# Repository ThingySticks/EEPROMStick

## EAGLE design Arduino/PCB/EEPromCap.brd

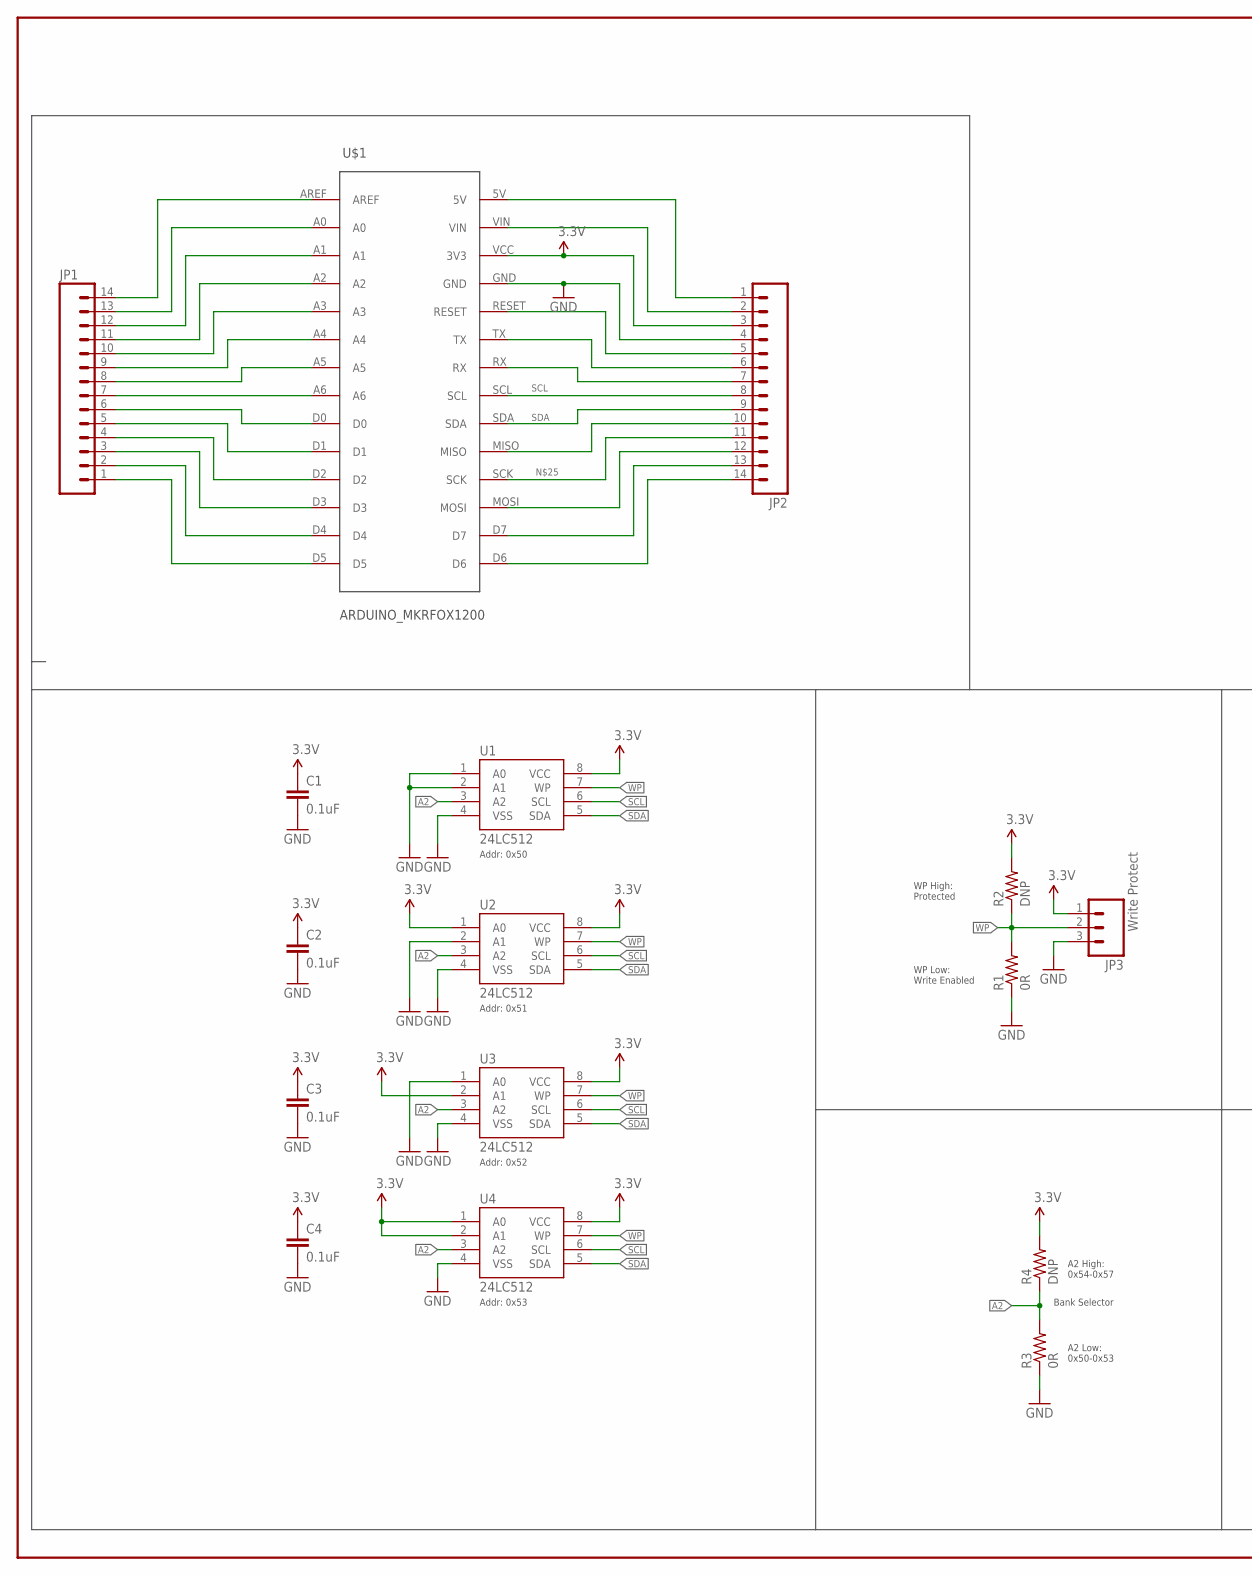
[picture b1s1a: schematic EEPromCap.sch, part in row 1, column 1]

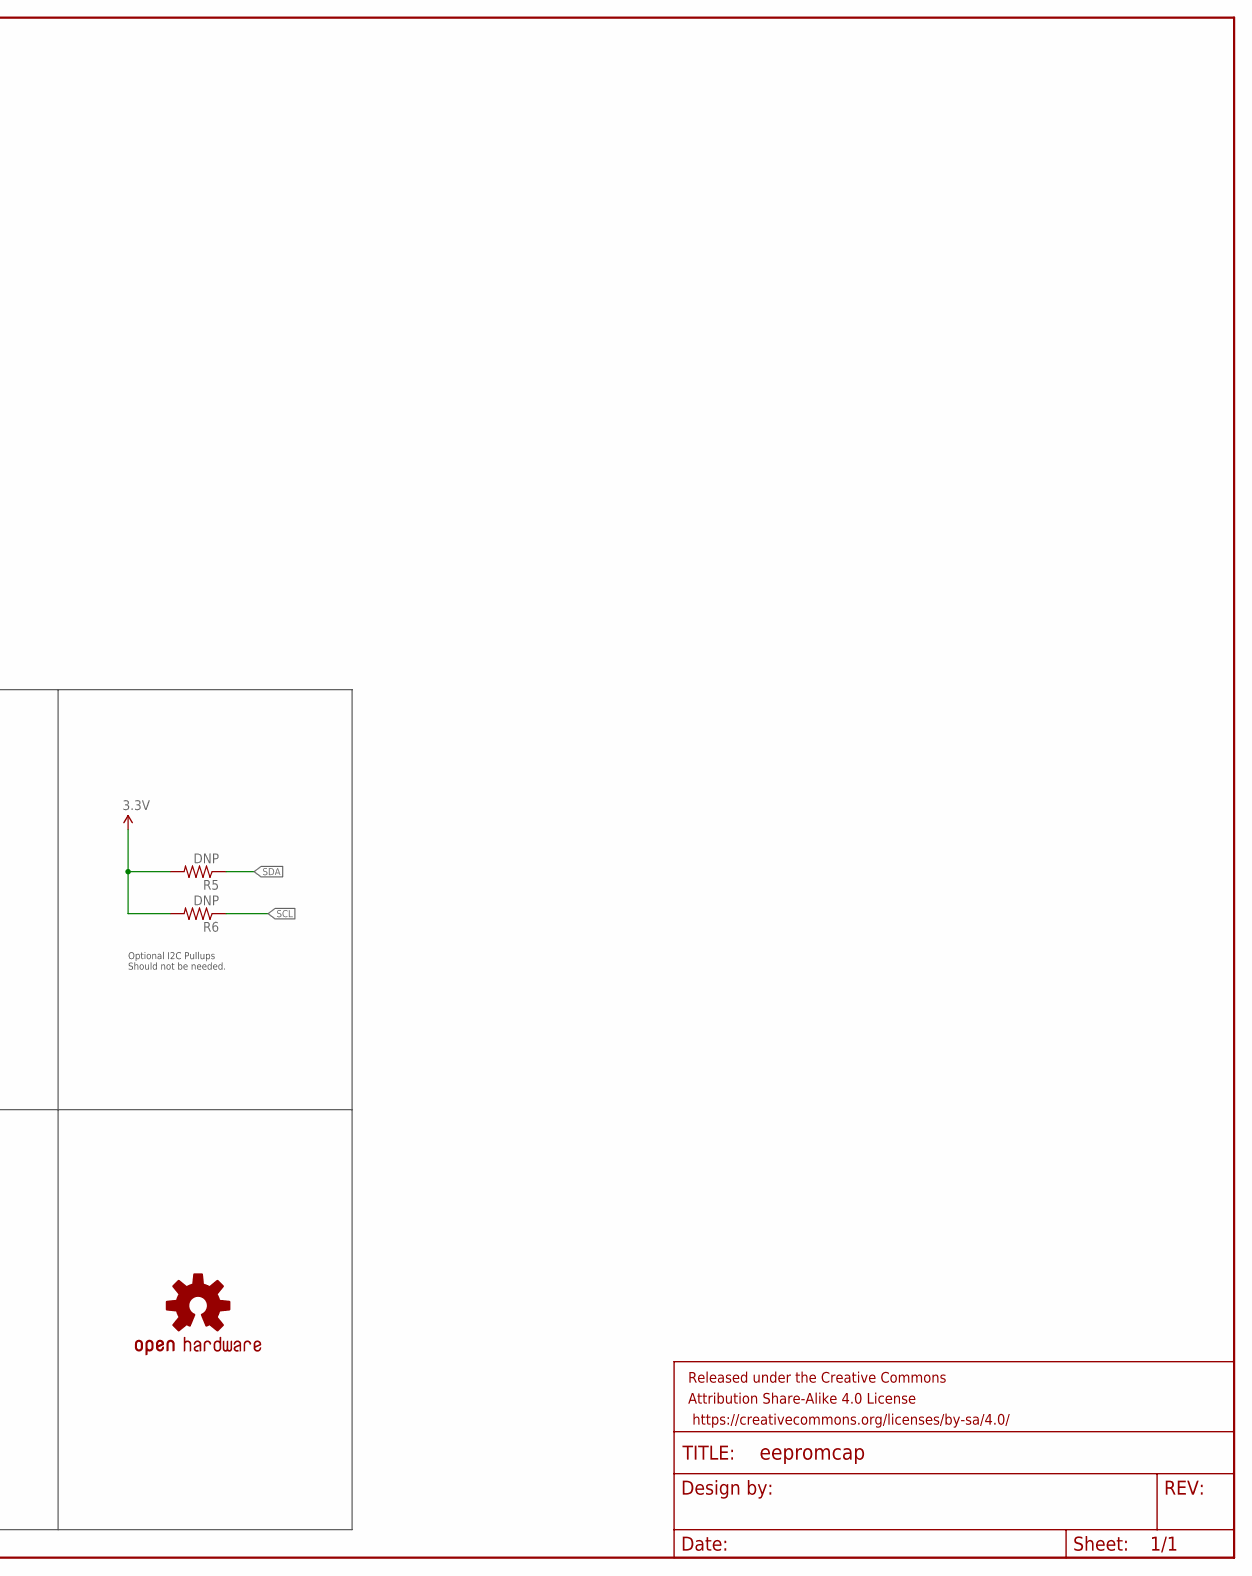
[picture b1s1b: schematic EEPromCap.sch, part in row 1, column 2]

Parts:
C1, C2, C3, C4: 0.1uF; 1206
FRAME1: FRAME-LEDGER; CREATIVE_COMMONS
JP1, JP2: M14; 1X14
JP3: Write Protect; 1X03
LOGO2: OSHW-LOGOM; OSHW-LOGO-M
R1, R3: 0R; 1206
R2, R4: DNP; 1206
R5, R6: DNP; 0805
U1, U2, U3, U4: 24LC512; SO08
U$1: ARDUINO_MKRFOX1200

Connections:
3.3V: C1.1, C2.1, C3.1, C4.1, JP2.3, JP3.1, R2.2, R4.2, R5.2, R6.2, U1.8 (VCC), U2.1 (A0), U2.8 (VCC), U3.2 (A1), U3.8 (VCC), U4.1 (A0), U4.2 (A1), U4.8 (VCC), U$1.VCC (3V3)
A2: R3.2, R4.1, U1.3 (A2), U2.3 (A2), U3.3 (A2), U4.3 (A2)
GND: C1.2, C2.2, C3.2, C4.2, JP2.4, JP3.3, R1.1, R3.1, U1.1 (A0), U1.2 (A1), U1.4 (VSS), U2.2 (A1), U2.4 (VSS), U3.1 (A0), U3.4 (VSS), U4.4 (VSS), U$1.GND
unnamed: JP1.14, U$1.AREF
unnamed: JP1.13, U$1.A0
unnamed: JP1.12, U$1.A1
unnamed: JP1.11, U$1.A2
unnamed: JP1.10, U$1.A3
unnamed: JP1.9, U$1.A4
unnamed: JP1.8, U$1.A5
unnamed: JP1.7, U$1.A6
unnamed: JP1.6, U$1.D0
unnamed: JP1.5, U$1.D1
unnamed: JP1.4, U$1.D2
unnamed: JP1.3, U$1.D3
unnamed: JP1.2, U$1.D4
unnamed: JP1.1, U$1.D5
unnamed: JP2.1, U$1.5V
unnamed: JP2.2, U$1.VIN
unnamed: JP2.5, U$1.RESET
unnamed: JP2.6, U$1.TX
unnamed: JP2.7, U$1.RX
unnamed: JP2.10, U$1.MISO
unnamed: JP2.11, U$1.SCK
unnamed: JP2.12, U$1.MOSI
unnamed: JP2.13, U$1.D7
unnamed: JP2.14, U$1.D6
SCL: JP2.8, R6.1, U1.6 (SCL), U2.6 (SCL), U3.6 (SCL), U4.6 (SCL), U$1.SCL
SDA: JP2.9, R5.1, U1.5 (SDA), U2.5 (SDA), U3.5 (SDA), U4.5 (SDA), U$1.SDA
WP: JP3.2, R1.2, R2.1, U1.7 (WP), U2.7 (WP), U3.7 (WP), U4.7 (WP)

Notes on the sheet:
Addr: 0x50
Addr: 0x51
Addr: 0x52
Addr: 0x53
Bank Selector
A2 Low: 0x50-0x53
A2 High: 0x54-0x57
WP High: Protected
WP Low: Write Enabled
Optional I2C Pullups Should not be needed.

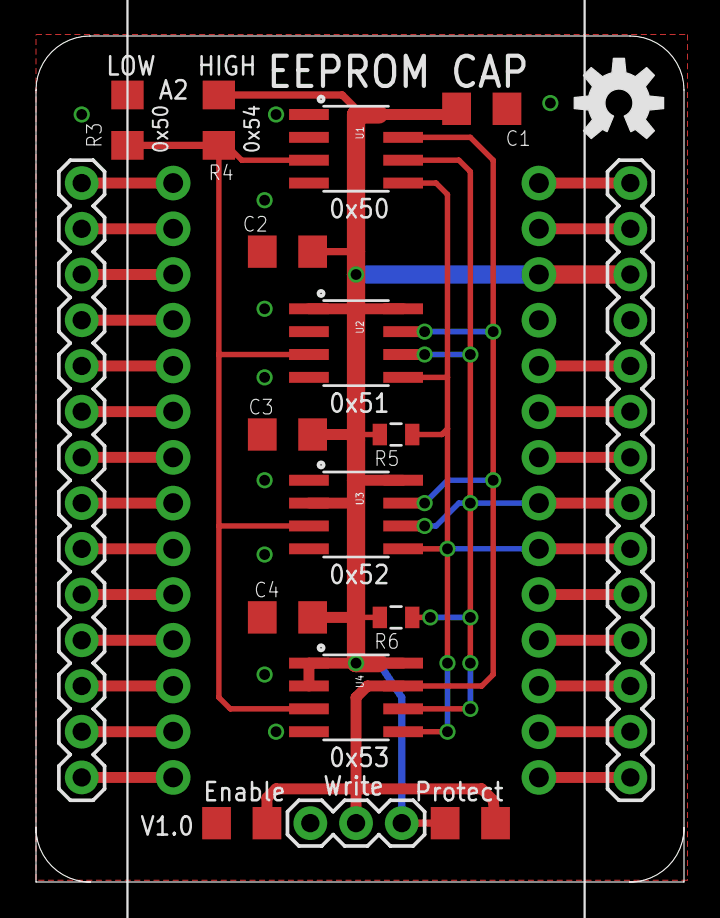
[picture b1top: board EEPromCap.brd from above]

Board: 2 copper layers, 36.0 x 47.0 mm, 20 parts (0 on the bottom side), 30 nets.

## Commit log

2018-01-23 First version as sent to DirtyPCBs

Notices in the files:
parts and their libraries:
SparkFun-Connectors: Licensing: Creative Commons ShareAlike 4.0 International - https://creativecommons.org/licenses/by-sa/4.0
SparkFun-Aesthetics: Released under the Creative Commons Attribution Share-Alike 4.0 License
SparkFun-Aesthetics: https://creativecommons.org/licenses/by-sa/4.0
